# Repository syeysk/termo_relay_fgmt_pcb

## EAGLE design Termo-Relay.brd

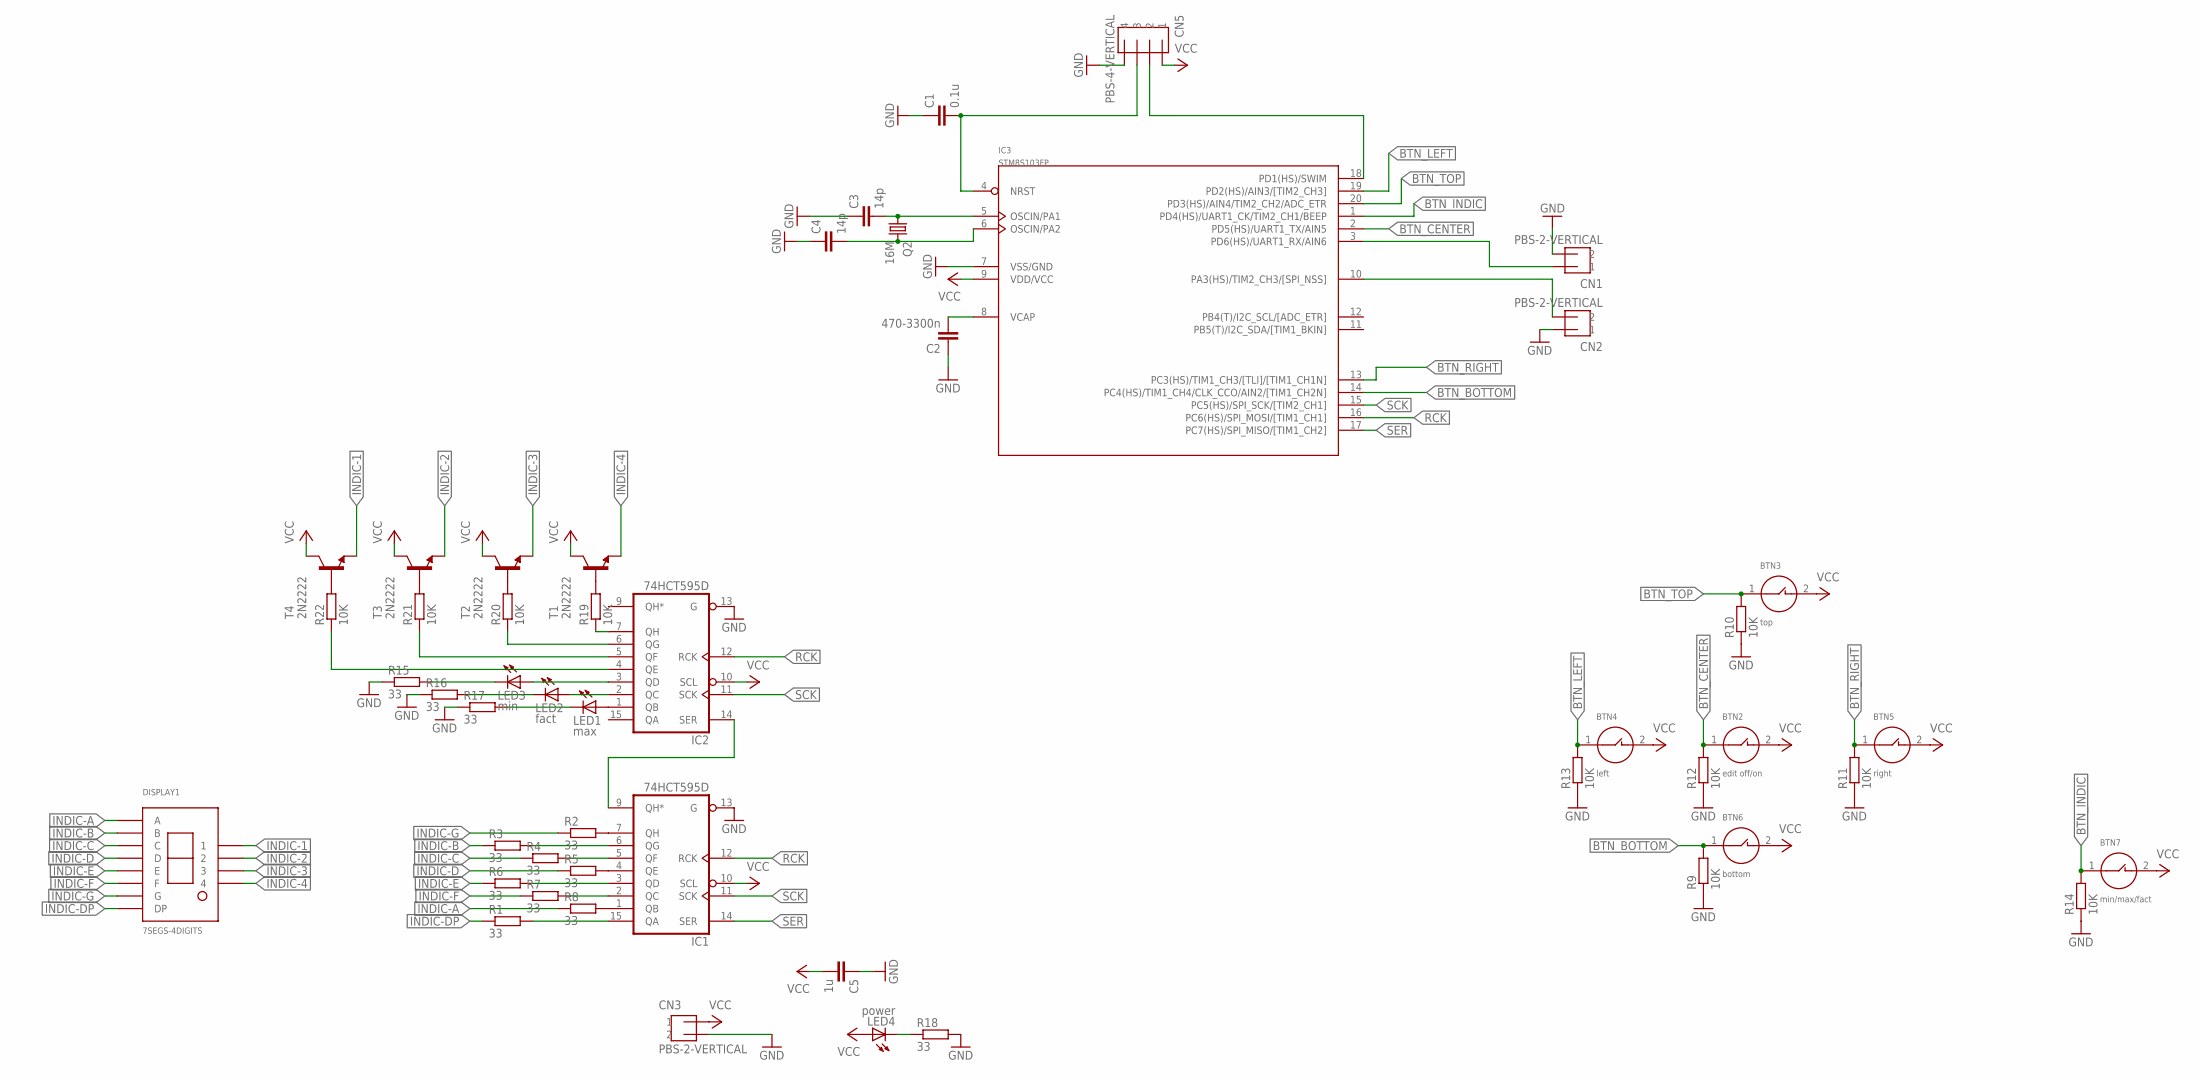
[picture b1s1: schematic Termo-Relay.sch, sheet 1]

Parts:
BTN2: edit off/on; BTN-6X4-SMD
BTN3: top; BTN-6X4-SMD
BTN4: left; BTN-6X4-SMD
BTN5: right; BTN-6X4-SMD
BTN6: bottom; BTN-6X4-SMD
BTN7: min/max/fact; BTN-6X4-SMD
C1: 0.1u; C0603
C2: 470-3300n; C0603
C3, C4: 14p; C0603
C5: 1u; C0603
CN1, CN2, CN3: PBS-2-VERTICAL
CN5: PBS-4-VERTICAL
DISPLAY1: 7SEGS-4DIGITS; 7SEG-4DIGITS
IC1, IC2: 74HCT595D; SO16
IC3: STM8S103FP; TSSOP20
LED1: max; LED3MM
LED2: fact; LED3MM
LED3: min; LED3MM
LED4: power; LED3MM
Q2: 16M; HC49GW
R1, R2, R3, R4, R5, R6, R7, R8, R15, R16, R17, R18: 33; R0603
R9, R10, R11, R12, R13, R14, R19, R20, R21, R22: 10K; R0603
T1, T2, T3, T4: 2N2222; SOT23-BEC

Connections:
BTN_BOTTOM: BTN6.1, IC3.14 (PC4(HS)/TIM1_CH4/CLK_CCO/AIN2/[TIM1_CH2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), R9.2
BTN_CENTER: BTN2.1, IC3.2 (PD5(HS)/UART1_TX/AIN5), R12.2
BTN_INDIC: BTN7.1, IC3.1 (PD4(HS)/UART1_CK/TIM2_CH1/BEEP), R14.2
BTN_LEFT: BTN4.1, IC3.19 (PD2(HS)/AIN3/[TIM2_CH3]), R13.2
BTN_RIGHT: BTN5.1, IC3.13 (PC3(HS)/TIM1_CH3/[TLI]/[TIM1_CH1N]), R11.2
BTN_TOP: BTN3.1, IC3.20 (PD3(HS)/AIN4/TIM2_CH2/ADC_ETR), R10.2
GND: C1.1, C2.1, C3.1, C4.1, C5.1, CN1.P$2 (2), CN2.P$1 (1), CN3.P$2 (2), CN5.P$4 (4), IC1.8 (GND), IC1.13 (G), IC2.8 (GND), IC2.13 (G), IC3.7 (VSS/GND), R9.1, R10.1, R11.1, R12.1, R13.1, R14.1, R15.1, R16.1, R17.1, R18.2
INDIC-1: DISPLAY1.1, T4.E
INDIC-2: DISPLAY1.2, T3.E
INDIC-3: DISPLAY1.3, T2.E
INDIC-4: DISPLAY1.4, T1.E
INDIC-A: DISPLAY1.A, R8.1
INDIC-B: DISPLAY1.B, R3.1
INDIC-C: DISPLAY1.C, R4.1
INDIC-D: DISPLAY1.D, R5.1
INDIC-DP: DISPLAY1.DP, R1.1
INDIC-E: DISPLAY1.E, R6.1
INDIC-F: DISPLAY1.F, R7.1
INDIC-G: DISPLAY1.G, R2.1
unnamed: IC1.9 (QH*), IC2.14 (SER)
unnamed: R19.2, T1.B
unnamed: R20.2, T2.B
unnamed: R21.2, T3.B
unnamed: R22.2, T4.B
unnamed: IC2.3 (QD), LED3.A
unnamed: IC2.2 (QC), LED2.A
unnamed: IC2.1 (QB), LED1.A
unnamed: C4.2, IC3.6 (OSCIN/PA2), Q2.2
unnamed: IC1.6 (QG), R3.2
unnamed: IC1.7 (QH), R2.2
unnamed: IC1.5 (QF), R4.2
unnamed: IC1.4 (QE), R5.2
unnamed: IC1.3 (QD), R6.2
unnamed: IC1.2 (QC), R7.2
unnamed: IC1.1 (QB), R8.2
unnamed: CN5.P$2 (2), IC3.18 (PD1(HS)/SWIM)
unnamed: CN1.P$1 (1), IC3.3 (PD6(HS)/UART1_RX/AIN6)
unnamed: C1.2, CN5.P$3 (3), IC3.4 (NRST)
unnamed: CN2.P$2 (2), IC3.10 (PA3(HS)/TIM2_CH3/[SPI_NSS])
unnamed: C2.2, IC3.8 (VCAP)
unnamed: IC1.15 (QA), R1.2
unnamed: LED3.K (C), R15.2
unnamed: LED2.K (C), R16.2
unnamed: LED1.K (C), R17.2
unnamed: C3.2, IC3.5 (OSCIN/PA1), Q2.1
unnamed: LED4.K (C), R18.1
unnamed: IC2.7 (QH), R19.1
unnamed: IC2.6 (QG), R20.1
unnamed: IC2.5 (QF), R21.1
unnamed: IC2.4 (QE), R22.1
RCK: IC1.12 (RCK), IC2.12 (RCK), IC3.16 (PC6(HS)/SPI_MOSI/[TIM1_CH1])
SCK: IC1.11 (SCK), IC2.11 (SCK), IC3.15 (PC5(HS)/SPI_SCK/[TIM2_CH1])
SER: IC1.14 (SER), IC3.17 (PC7(HS)/SPI_MISO/[TIM1_CH2])
VCC: BTN2.2, BTN3.2, BTN4.2, BTN5.2, BTN6.2, BTN7.2, C5.2, CN3.P$1 (1), CN5.P$1 (1), IC1.10 (SCL), IC1.16 (VCC), IC2.10 (SCL), IC2.16 (VCC), IC3.9 (VDD/VCC), LED4.A, T1.C, T2.C, T3.C, T4.C

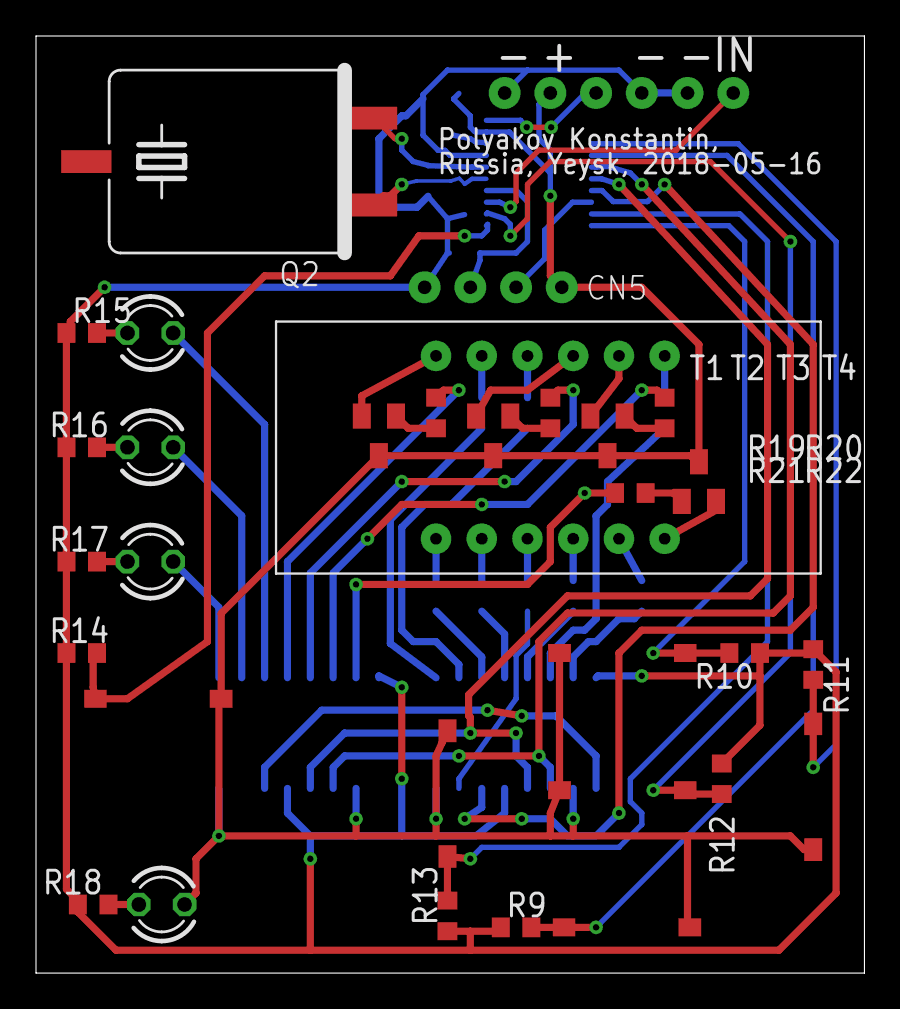
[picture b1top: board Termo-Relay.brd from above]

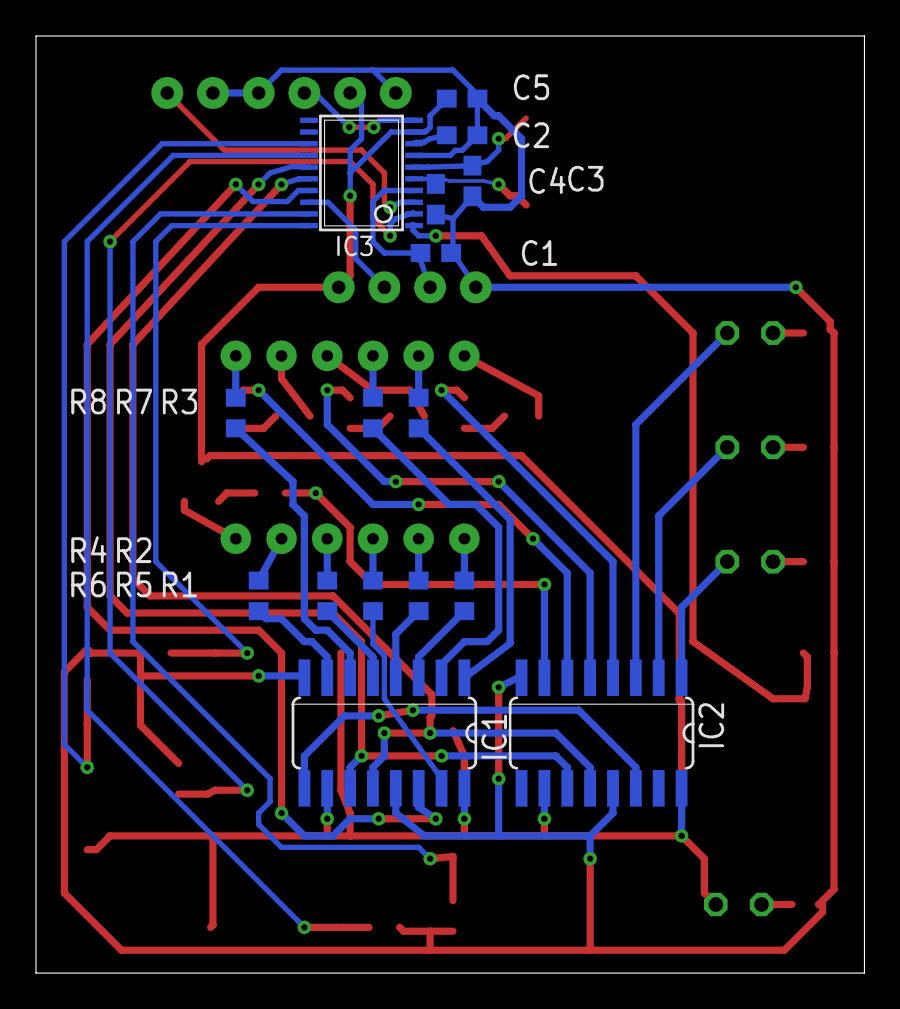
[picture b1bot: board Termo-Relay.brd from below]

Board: 2 copper layers, 46.0 x 52.1 mm, 50 parts (16 on the bottom side), 54 nets.

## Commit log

2018-05-13 Pins for sensor and heater was added on the scheme. Routes for crystal was added on the pcb.
2018-05-13 Capaxcitors were added/ PCB routers for stym8 were added
2018-05-13 LICENCE was added
2018-05-14 Roads for RCK, SCK and SER (between stm8 and hc595) were added
2018-05-14 size of the board was smalled
2018-05-15 Roads for buttons and power were added. One error (center button was not connected to STM) was corrected
2018-05-15 Tracing was finished.
2018-05-15 Some angles was corrected.
2018-05-16 silk was normalized. Author was added
2018-08-30 replacing into layer 25
2023-11-26 change gitignore
2023-11-26 add gerbers
